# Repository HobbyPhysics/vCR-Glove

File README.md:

# vCR-Glove
Open-source vibrotactile coordinated reset glove hardware, firmware, and fabrication files

## License

The hardware design files in the `PCB/` and `3D_Printing/` directories are licensed under the CERN Open Hardware Licence Version 2 - Permissive (CERN-OHL-P-2.0). See `LICENSE-HARDWARE.txt`.

The firmware in the `Firmware/` directory is licensed under the MIT License. See `Firmware/LICENSE.txt`.

These licenses permit commercial use of the designs and firmware subject to the terms of the respective licenses. No warranty is provided.

## Project Status

This project is under active development. Design files and documentation may be updated as testing progresses.

## Construction and Technical Experience

This project requires experience with electronic assembly, soldering, PCB fabrication and assembly services, microcontroller programming, and mechanical fabrication.

The documentation and design files are provided to allow technically experienced users to reproduce or modify the project. They are not intended to provide comprehensive instruction in the underlying fabrication and assembly techniques.

Users who do not have experience with these techniques are encouraged to obtain assistance from someone familiar with electronic assembly and fabrication.

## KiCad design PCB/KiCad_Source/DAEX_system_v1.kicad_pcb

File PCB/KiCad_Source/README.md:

# KiCad Source Files
# KiCad Source Files

This directory contains the editable KiCad source files for the vCR Glove printed circuit board.

The project was created using KiCad. To open the complete project, start KiCad and open the `.kicad_pro` project file. The schematic and PCB layout can then be opened from the KiCad Project Manager.

## Files

- `.kicad_pro` - KiCad project file
- `.kicad_sch` - schematics
- `.kicad_pcb` - PCB layout

## Schematic DNP Markings

Some components in the schematic are marked with a red X. These components have been designated **DNP (Do Not Populate)** in KiCad.

The components are intentionally retained in the schematic but are not installed on the manufactured PCB. The red X is therefore not an error indication. It provides a visual record of optional or unused components and identifies the configuration used for production.

## Viewing the PCB

Open the `.kicad_pcb` file from the KiCad Project Manager to view the PCB layout.

KiCad can also display a three-dimensional representation of the assembled PCB. With the PCB Editor open, select:

**View → 3D Viewer**

The 3D Viewer can be rotated and zoomed to inspect the component placement and overall board assembly.

## Manufacturing Files

The files used to order the PCB and assembled board are provided separately in:

`../JLCPCB_Production/`

Those production files should be used for reproducing the manufactured board. The files in this directory are provided for viewing or modifying the design.

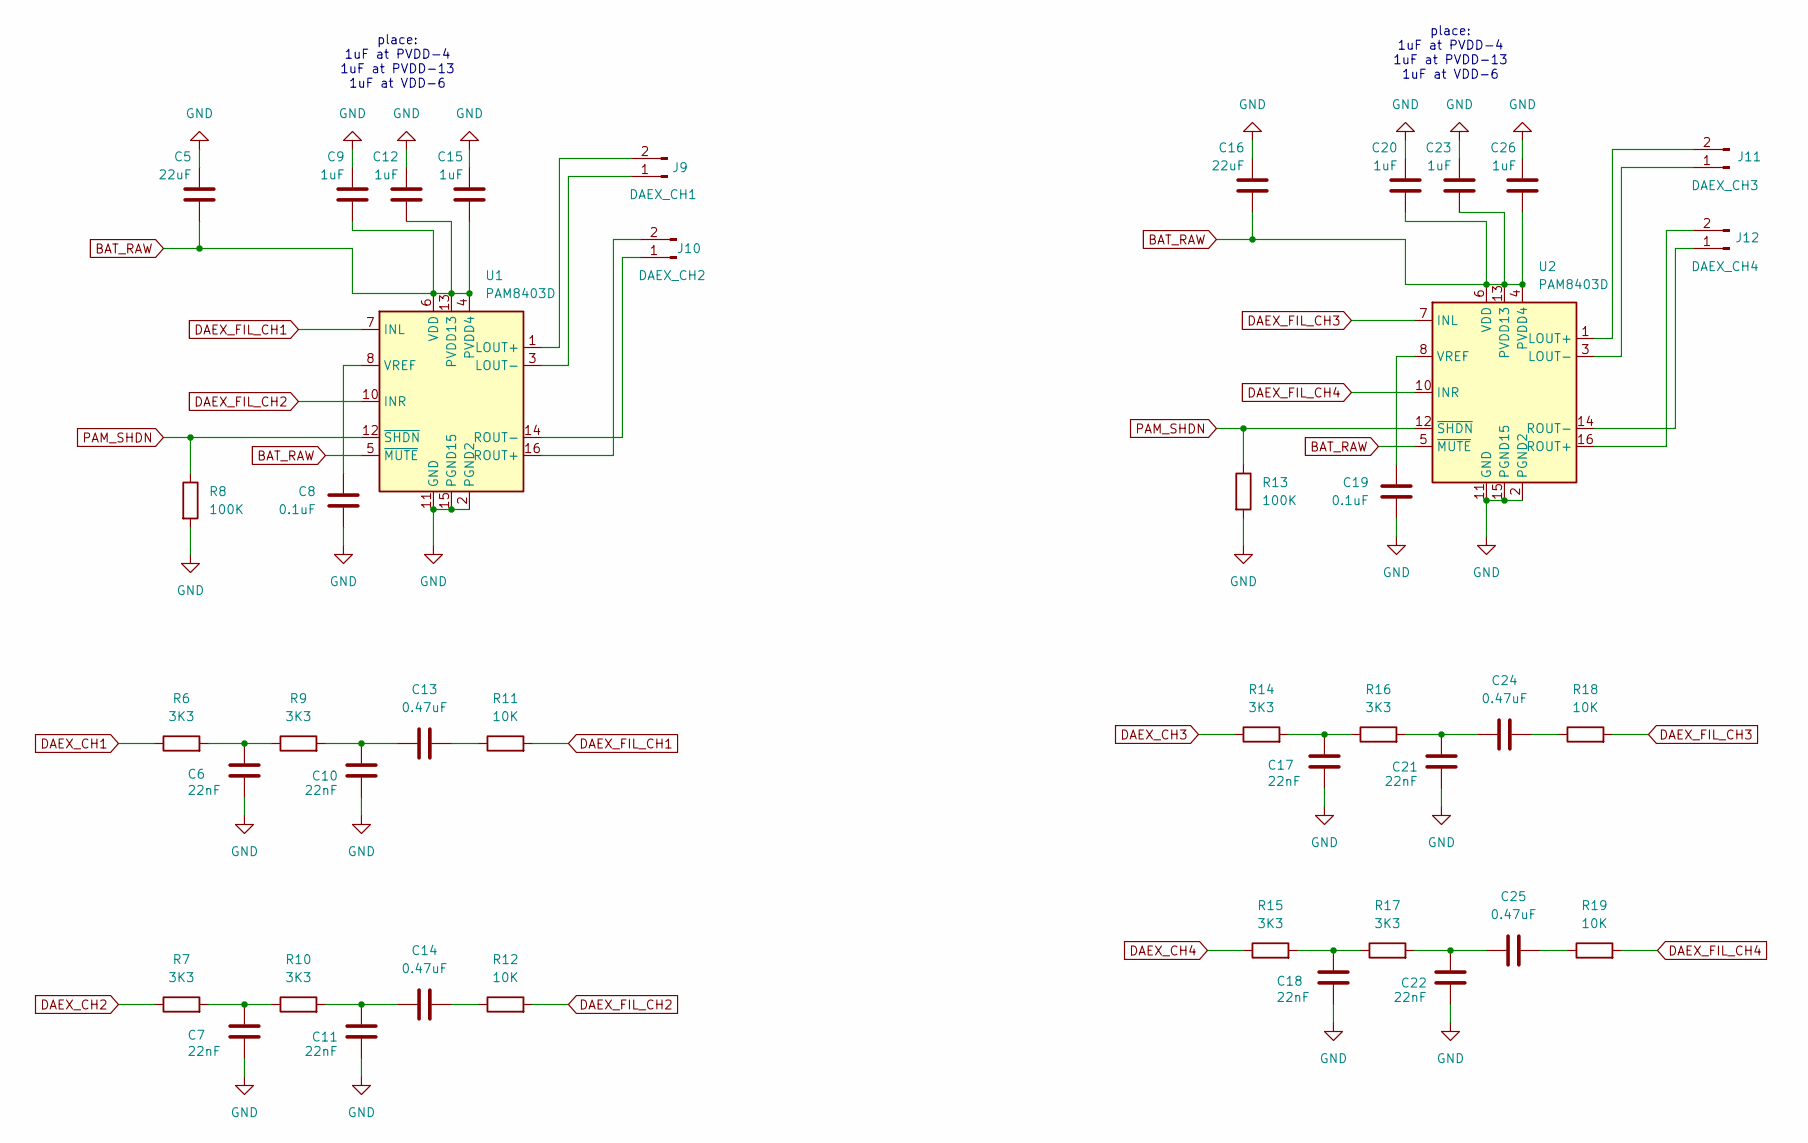
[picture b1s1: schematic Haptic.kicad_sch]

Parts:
C5, C16: 22uF; C_1206_3216Metric
C6, C7, C10, C11, C17, C18, C21, C22: 22nF; C_0805_2012Metric
C8, C19: 0.1uF; C_0805_2012Metric
C9, C12, C15, C20, C23, C26: 1uF; C_0805_2012Metric
C13, C14, C24, C25: 0.47uF; C_0805_2012Metric
J9: DAEX_CH1; JST_PH_S2B-PH-K_1x02_P2.00mm_Horizontal
J10: DAEX_CH2; JST_PH_S2B-PH-K_1x02_P2.00mm_Horizontal
J11: DAEX_CH3; JST_PH_S2B-PH-K_1x02_P2.00mm_Horizontal
J12: DAEX_CH4; JST_PH_S2B-PH-K_1x02_P2.00mm_Horizontal
R6, R7, R9, R10, R14, R15, R16, R17: 3K3; R_0805_2012Metric
R8, R13: 100K; R_0805_2012Metric
R11, R12, R18, R19: 10K; R_0805_2012Metric
U1, U2: PAM8403D; SOIC-16_3.9x9.9mm_P1.27mm

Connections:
BAT_RAW: C5.1, C9.1, C12.1, C15.1, C16.1, C20.1, C23.1, C26.1, U1.4 (PVDD4), U1.5 (~MUTE), U1.6 (VDD), U1.13 (PVDD13), U2.4 (PVDD4), U2.5 (~MUTE), U2.6 (VDD), U2.13 (PVDD13); also elsewhere on the board
DAEX_CH1: R6.1; also elsewhere on the board
DAEX_CH2: R7.1; also elsewhere on the board
DAEX_CH3: R14.1; also elsewhere on the board
DAEX_CH4: R15.1; also elsewhere on the board
DAEX_FIL_CH1: R11.2, U1.7 (INL)
DAEX_FIL_CH2: R12.2, U1.10 (INR)
DAEX_FIL_CH3: R18.2, U2.7 (INL)
DAEX_FIL_CH4: R19.2, U2.10 (INR)
GND: C5.2, C6.1, C7.1, C8.1, C9.2, C10.1, C11.1, C12.2, C15.2, C16.2, C17.1, C18.1, C19.1, C20.2, C21.1, C22.1, C23.2, C26.2, R8.2, R13.2, U1.2 (PGND2), U1.11 (GND), U1.15 (PGND15), U2.2 (PGND2), U2.11 (GND), U2.15 (PGND15); also elsewhere on the board
unnamed: C6.2, R6.2, R9.1
unnamed: C7.2, R7.2, R10.1
unnamed: C10.2, C13.1, R9.2
unnamed: C11.2, C14.1, R10.2
unnamed: C13.2, R11.1
unnamed: C14.2, R12.1
unnamed: C17.2, R14.2, R16.1
unnamed: C18.2, R15.2, R17.1
unnamed: C21.2, C24.1, R16.2
unnamed: C22.2, C25.1, R17.2
unnamed: C24.2, R18.1
unnamed: C25.2, R19.1
unnamed: J9.1, U1.3 (LOUT-)
unnamed: J9.2, U1.1 (LOUT+)
unnamed: J10.1, U1.14 (ROUT-)
unnamed: J10.2, U1.16 (ROUT+)
unnamed: J11.1, U2.3 (LOUT-)
unnamed: J11.2, U2.1 (LOUT+)
unnamed: J12.1, U2.14 (ROUT-)
unnamed: J12.2, U2.16 (ROUT+)
unnamed: C8.2, U1.8 (VREF)
unnamed: C19.2, U2.8 (VREF)
PAM_SHDN: R8.1, R13.1, U1.12 (~SHDN), U2.12 (~SHDN); also elsewhere on the board

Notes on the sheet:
place: 1uF at PVDD-4 1uF at PVDD-13 1uF at VDD-6

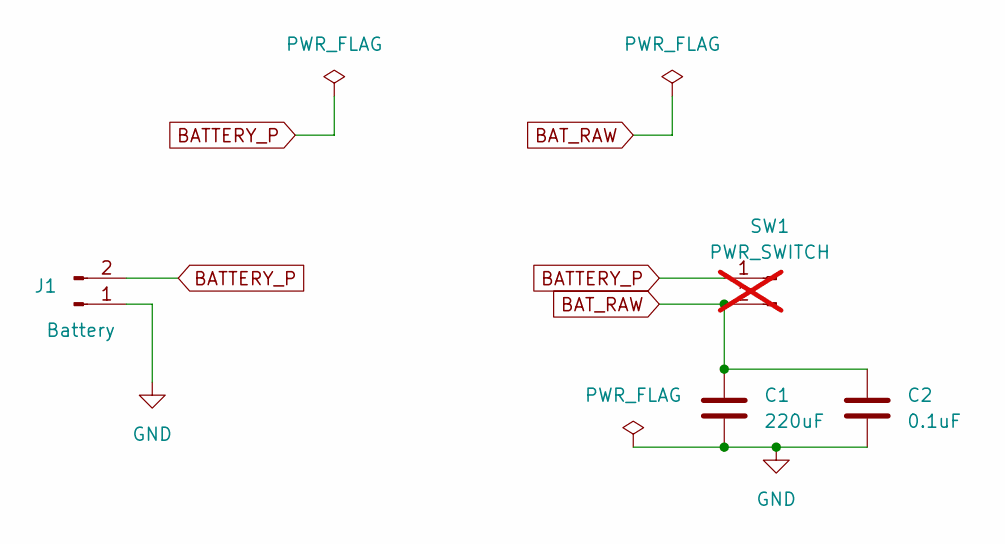
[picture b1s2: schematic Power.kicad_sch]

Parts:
C1: 220uF; CP_Elec_6.3x5.4
C2: 0.1uF; C_0805_2012Metric
J1: Battery; JST_PH_S2B-PH-K_1x02_P2.00mm_Horizontal
SW1: PWR_SWITCH; SolderWire-0.5sqmm_1x02_P4.6mm_D0.9mm_OD2.1mm; not fitted

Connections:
BATTERY_P: J1.2, SW1.1
BAT_RAW: C1.1, C2.1, SW1.2; also elsewhere on the board
GND: C1.2, C2.2, J1.1; also elsewhere on the board

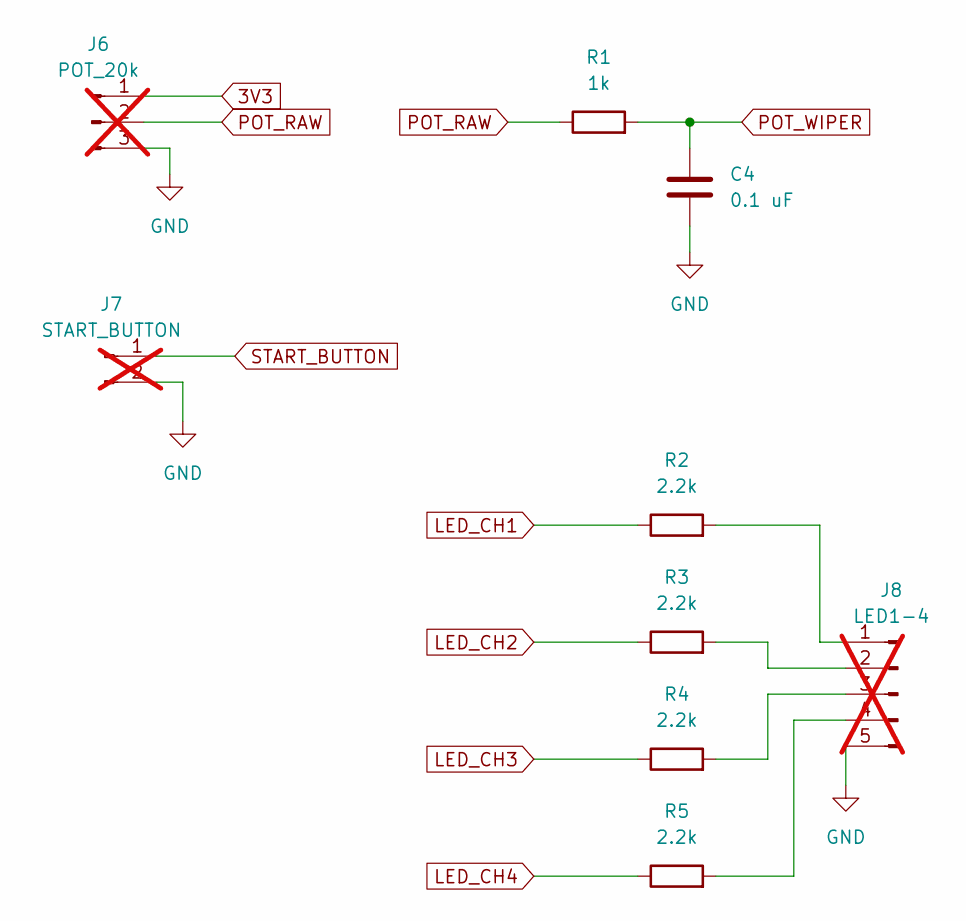
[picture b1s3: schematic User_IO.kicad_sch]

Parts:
C4: 0.1 uF; C_0805_2012Metric
J6: POT_20k; SolderWire-0.5sqmm_1x03_P4.6mm_D0.9mm_OD2.1mm; not fitted
J7: START_BUTTON; SolderWire-0.5sqmm_1x02_P4.6mm_D0.9mm_OD2.1mm; not fitted
J8: LED1-4; PinHeader_1x05_P2.54mm_Vertical; not fitted
R1: 1k; R_0805_2012Metric
R2, R3, R4, R5: 2.2k; R_0805_2012Metric

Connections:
3V3: J6.1; also elsewhere on the board
GND: C4.2, J6.3, J7.2, J8.5; also elsewhere on the board
LED_CH1: R2.1; also elsewhere on the board
LED_CH2: R3.1; also elsewhere on the board
LED_CH3: R4.1; also elsewhere on the board
LED_CH4: R5.1; also elsewhere on the board
unnamed: J8.1, R2.2
unnamed: J8.2, R3.2
unnamed: J8.3, R4.2
unnamed: J8.4, R5.2
POT_RAW: J6.2, R1.1
POT_WIPER: C4.1, R1.2; also elsewhere on the board
START_BUTTON: J7.1; also elsewhere on the board

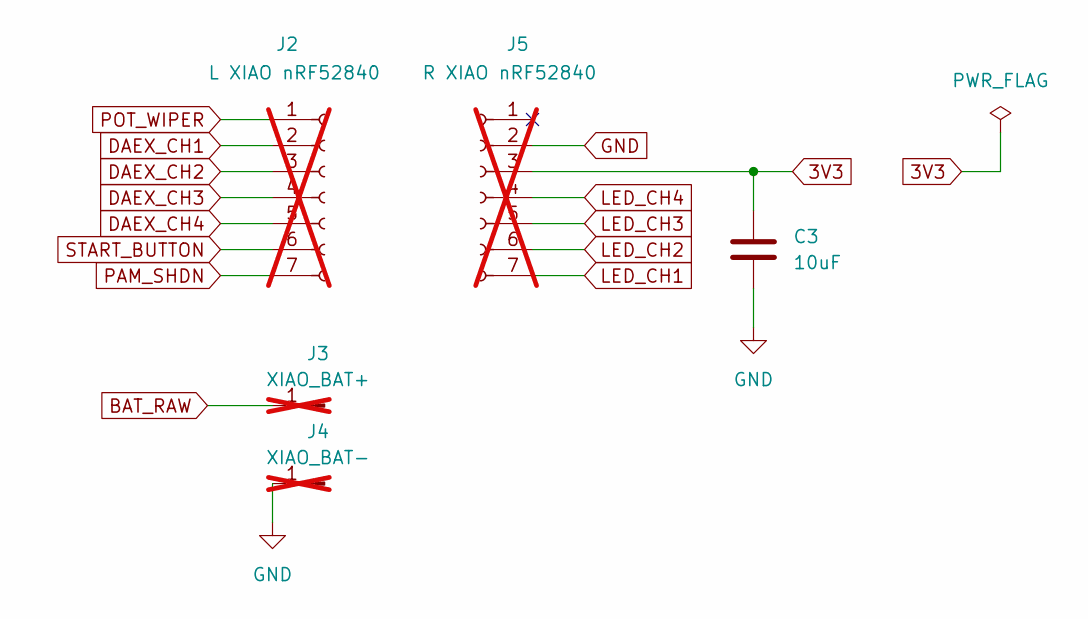
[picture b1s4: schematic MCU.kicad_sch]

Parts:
C3: 10uF; C_0805_2012Metric
J2: L XIAO nRF52840; PinHeader_1x07_P2.54mm_Vertical; not fitted
J3: XIAO_BAT+; SolderWire-0.5sqmm_1x01_D0.9mm_OD2.1mm; not fitted
J4: XIAO_BAT-; SolderWire-0.5sqmm_1x01_D0.9mm_OD2.1mm; not fitted
J5: R XIAO nRF52840; PinHeader_1x07_P2.54mm_Vertical; not fitted

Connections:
3V3: C3.1, J5.3; also elsewhere on the board
BAT_RAW: J3.1; also elsewhere on the board
DAEX_CH1: J2.2; also elsewhere on the board
DAEX_CH2: J2.3; also elsewhere on the board
DAEX_CH3: J2.4; also elsewhere on the board
DAEX_CH4: J2.5; also elsewhere on the board
GND: C3.2, J4.1, J5.2; also elsewhere on the board
LED_CH1: J5.7; also elsewhere on the board
LED_CH2: J5.6; also elsewhere on the board
LED_CH3: J5.5; also elsewhere on the board
LED_CH4: J5.4; also elsewhere on the board
PAM_SHDN: J2.7; also elsewhere on the board
POT_WIPER: J2.1; also elsewhere on the board
START_BUTTON: J2.6; also elsewhere on the board

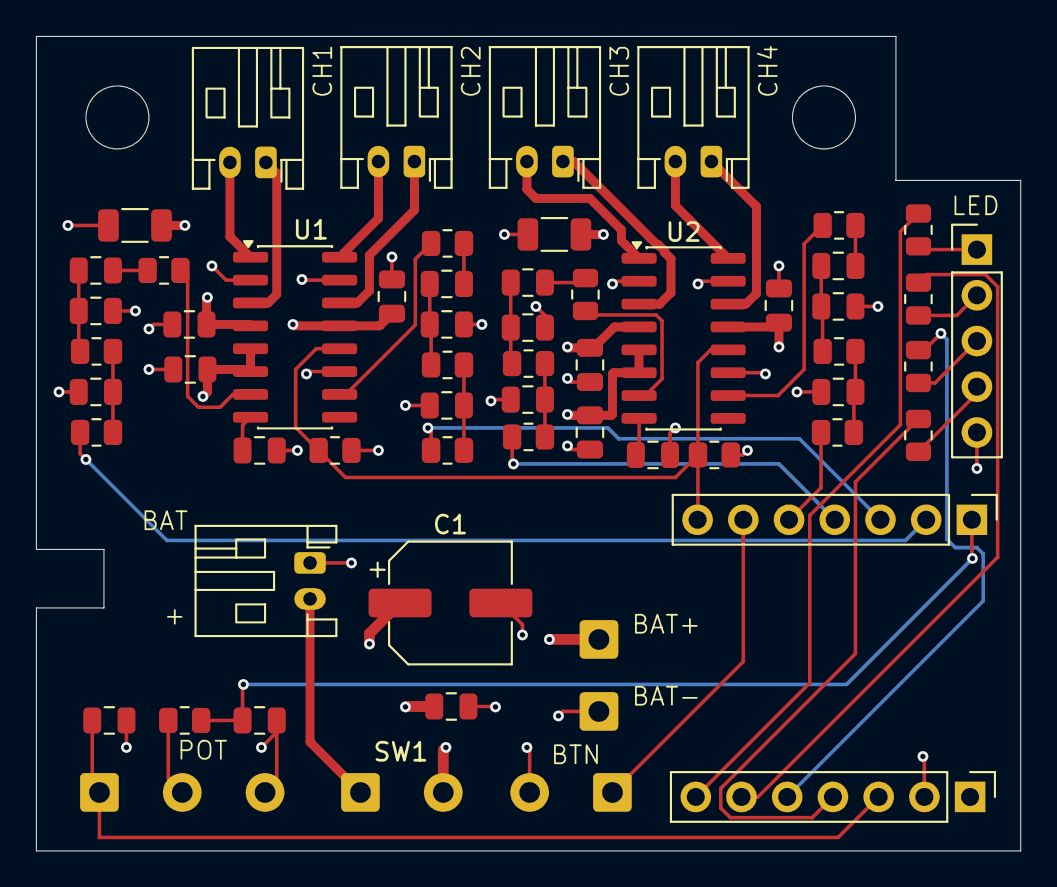
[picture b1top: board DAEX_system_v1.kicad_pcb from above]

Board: 4 copper layers, 54.7 x 45.2 mm, 62 parts (0 on the bottom side), 46 nets.

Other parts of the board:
H1, H2: MountingHole_3.5mm

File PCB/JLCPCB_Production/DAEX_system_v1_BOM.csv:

Comment,Designator,Footprint,JLCPCB Part #
PAM8403DR-H,"U1,U2",SOIC-16_3.9x9.9mm_P1.27mm,C17337
DAEX_CH1,"J9, J11, J12, J10, J1",JST_PH_S2B-PH-K_1x02_P2.00mm_Horizontal,C173752
10K,"R19,R18,R12,R11",R_0805_2012Metric,C176201
3.3k,"R17,R16,R15,R14,R6,R9,R10,R7",R_0805_2012Metric,C26010
100K,"R13,R8",R_0805_2012Metric,C22356675
1k,R1,R_0805_2012Metric,C22356679
2.2k,"R3,R5,R4,R2",R_0805_2012Metric,C17520
1uF,"C26,C23,C20,C12,C15,C9",C_0805_2012Metric,C28323
470nF,"C25,C24,C13,C14",C_0805_2012Metric,C1778
22nF,"C22,C21,C6,C17,C11,C7,C18,C10",C_0805_2012Metric,C1729
22nF,"C5, C16",C_1206_3216Metric,C1856
100nF,"C19,C2,C8,C4",C_0805_2012Metric,C49678
10uF,C3,C_0805_2012Metric,C15850
220uF,C1,CP_Elec_6.3x5.4,C3345
